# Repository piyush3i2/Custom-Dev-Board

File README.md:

# Custom-Dev-Board
This project focuses on designing and building a custom development board that combines the strengths of the Raspberry Pi RP2040 microcontroller and an Espressif Systems ESP32 Wi-Fi/Bluetooth module on a single PCB. The goal is to create a compact, flexible, and cost-effective devboard suitable for IoT, embedded systems.

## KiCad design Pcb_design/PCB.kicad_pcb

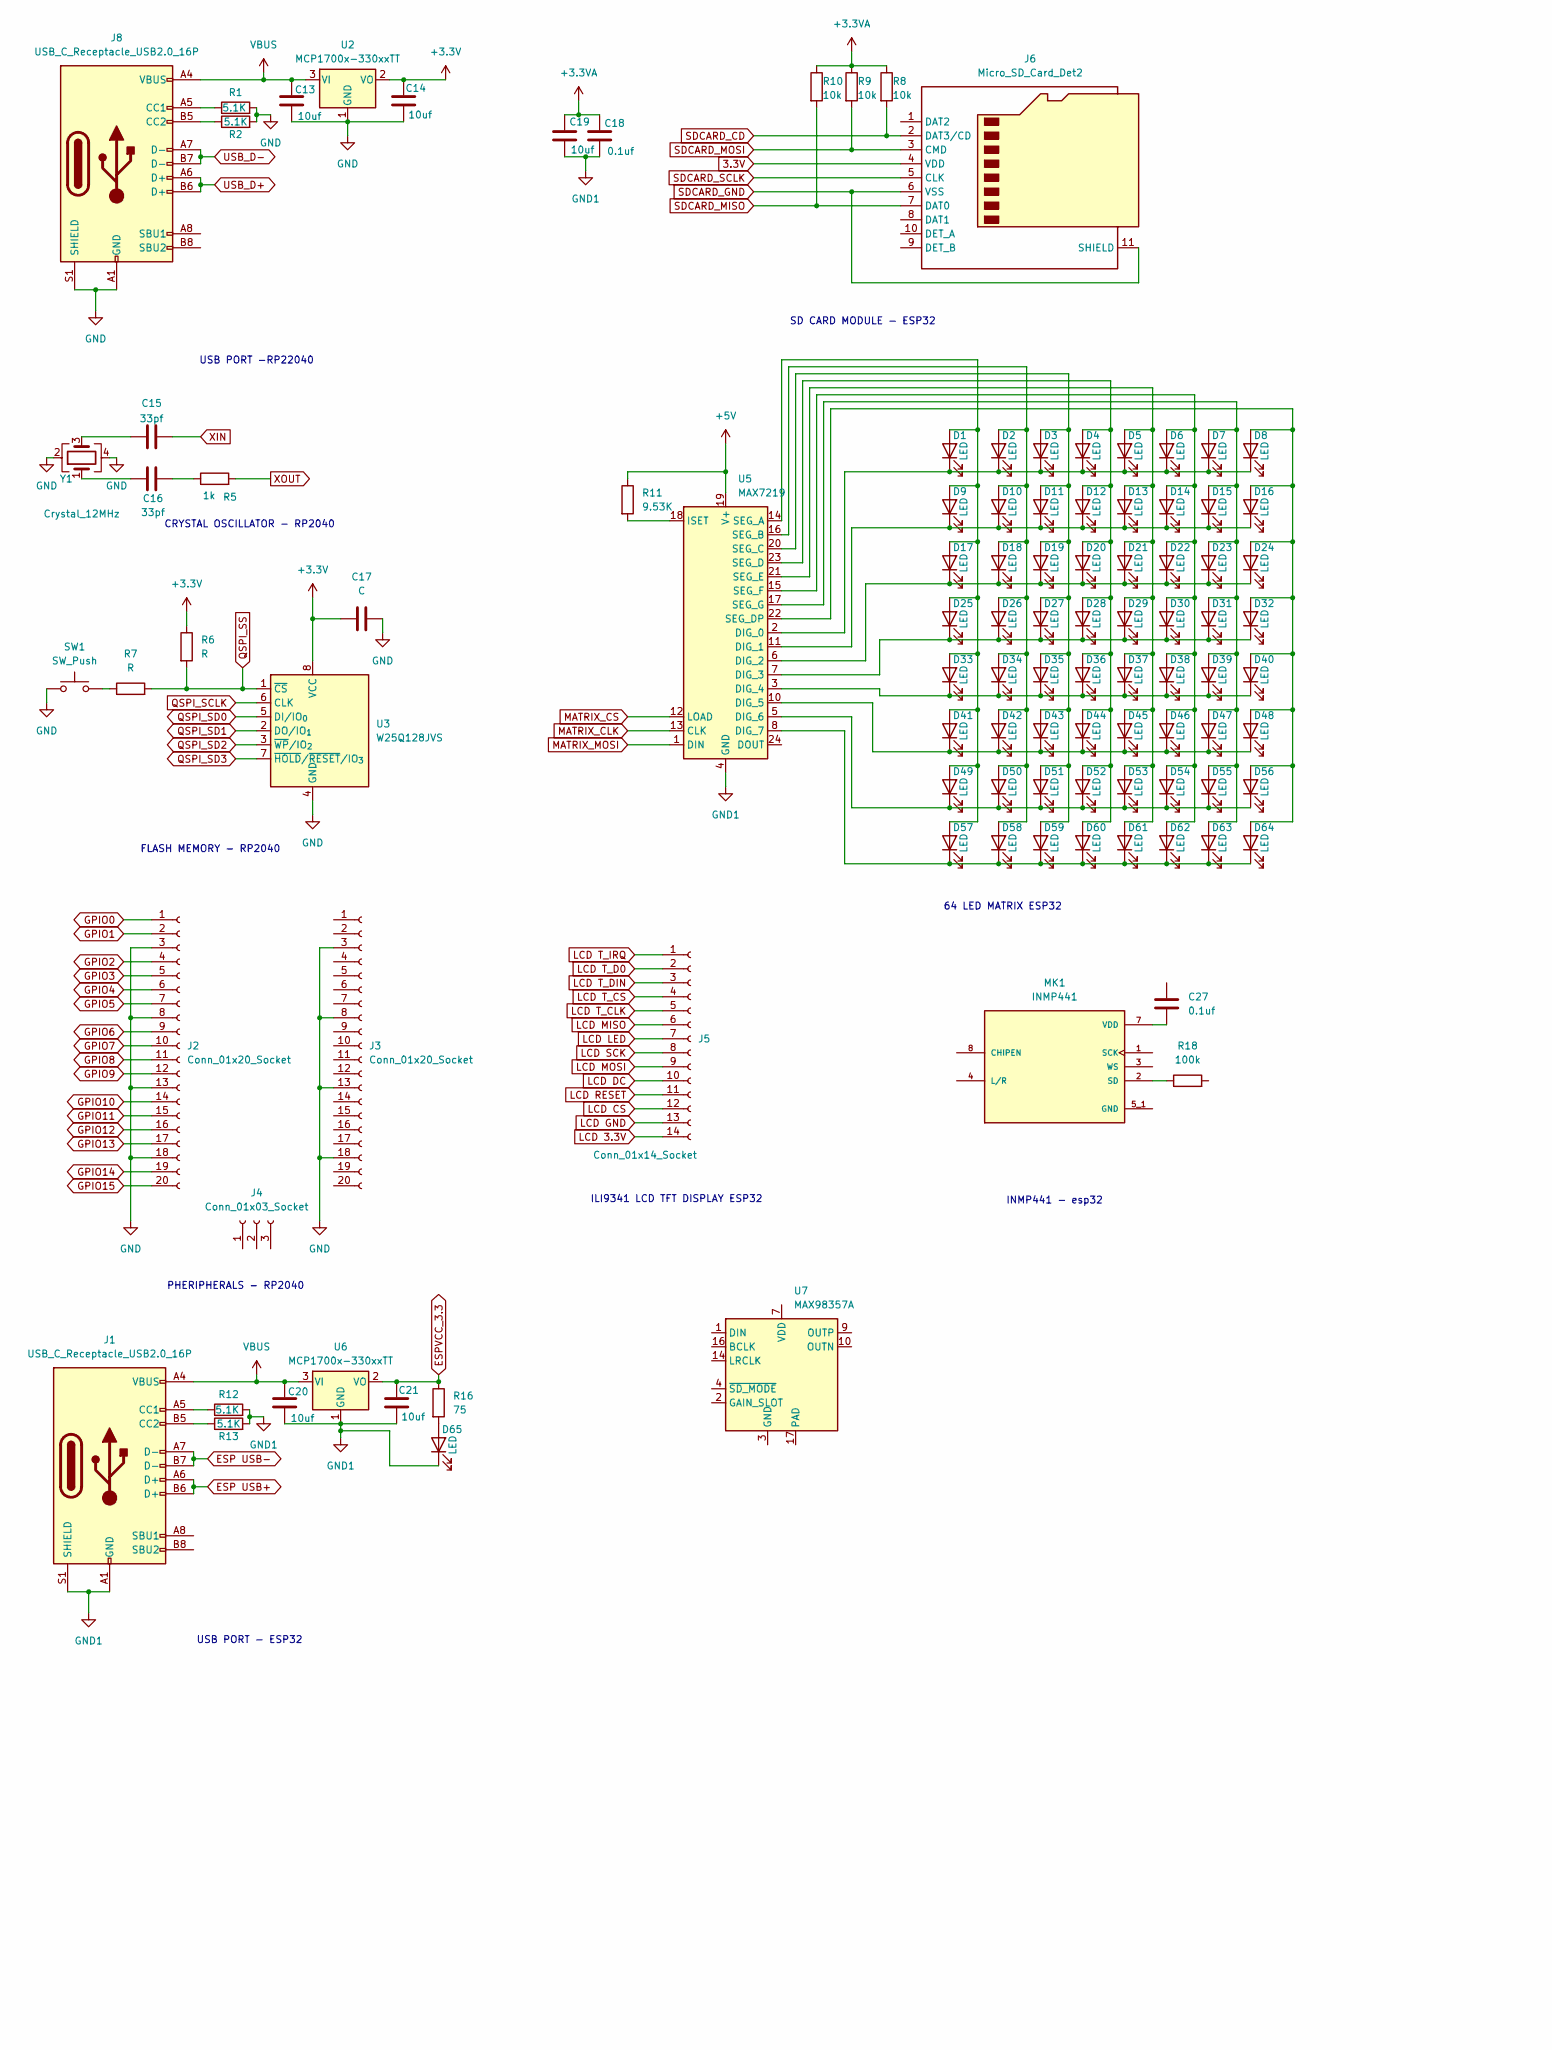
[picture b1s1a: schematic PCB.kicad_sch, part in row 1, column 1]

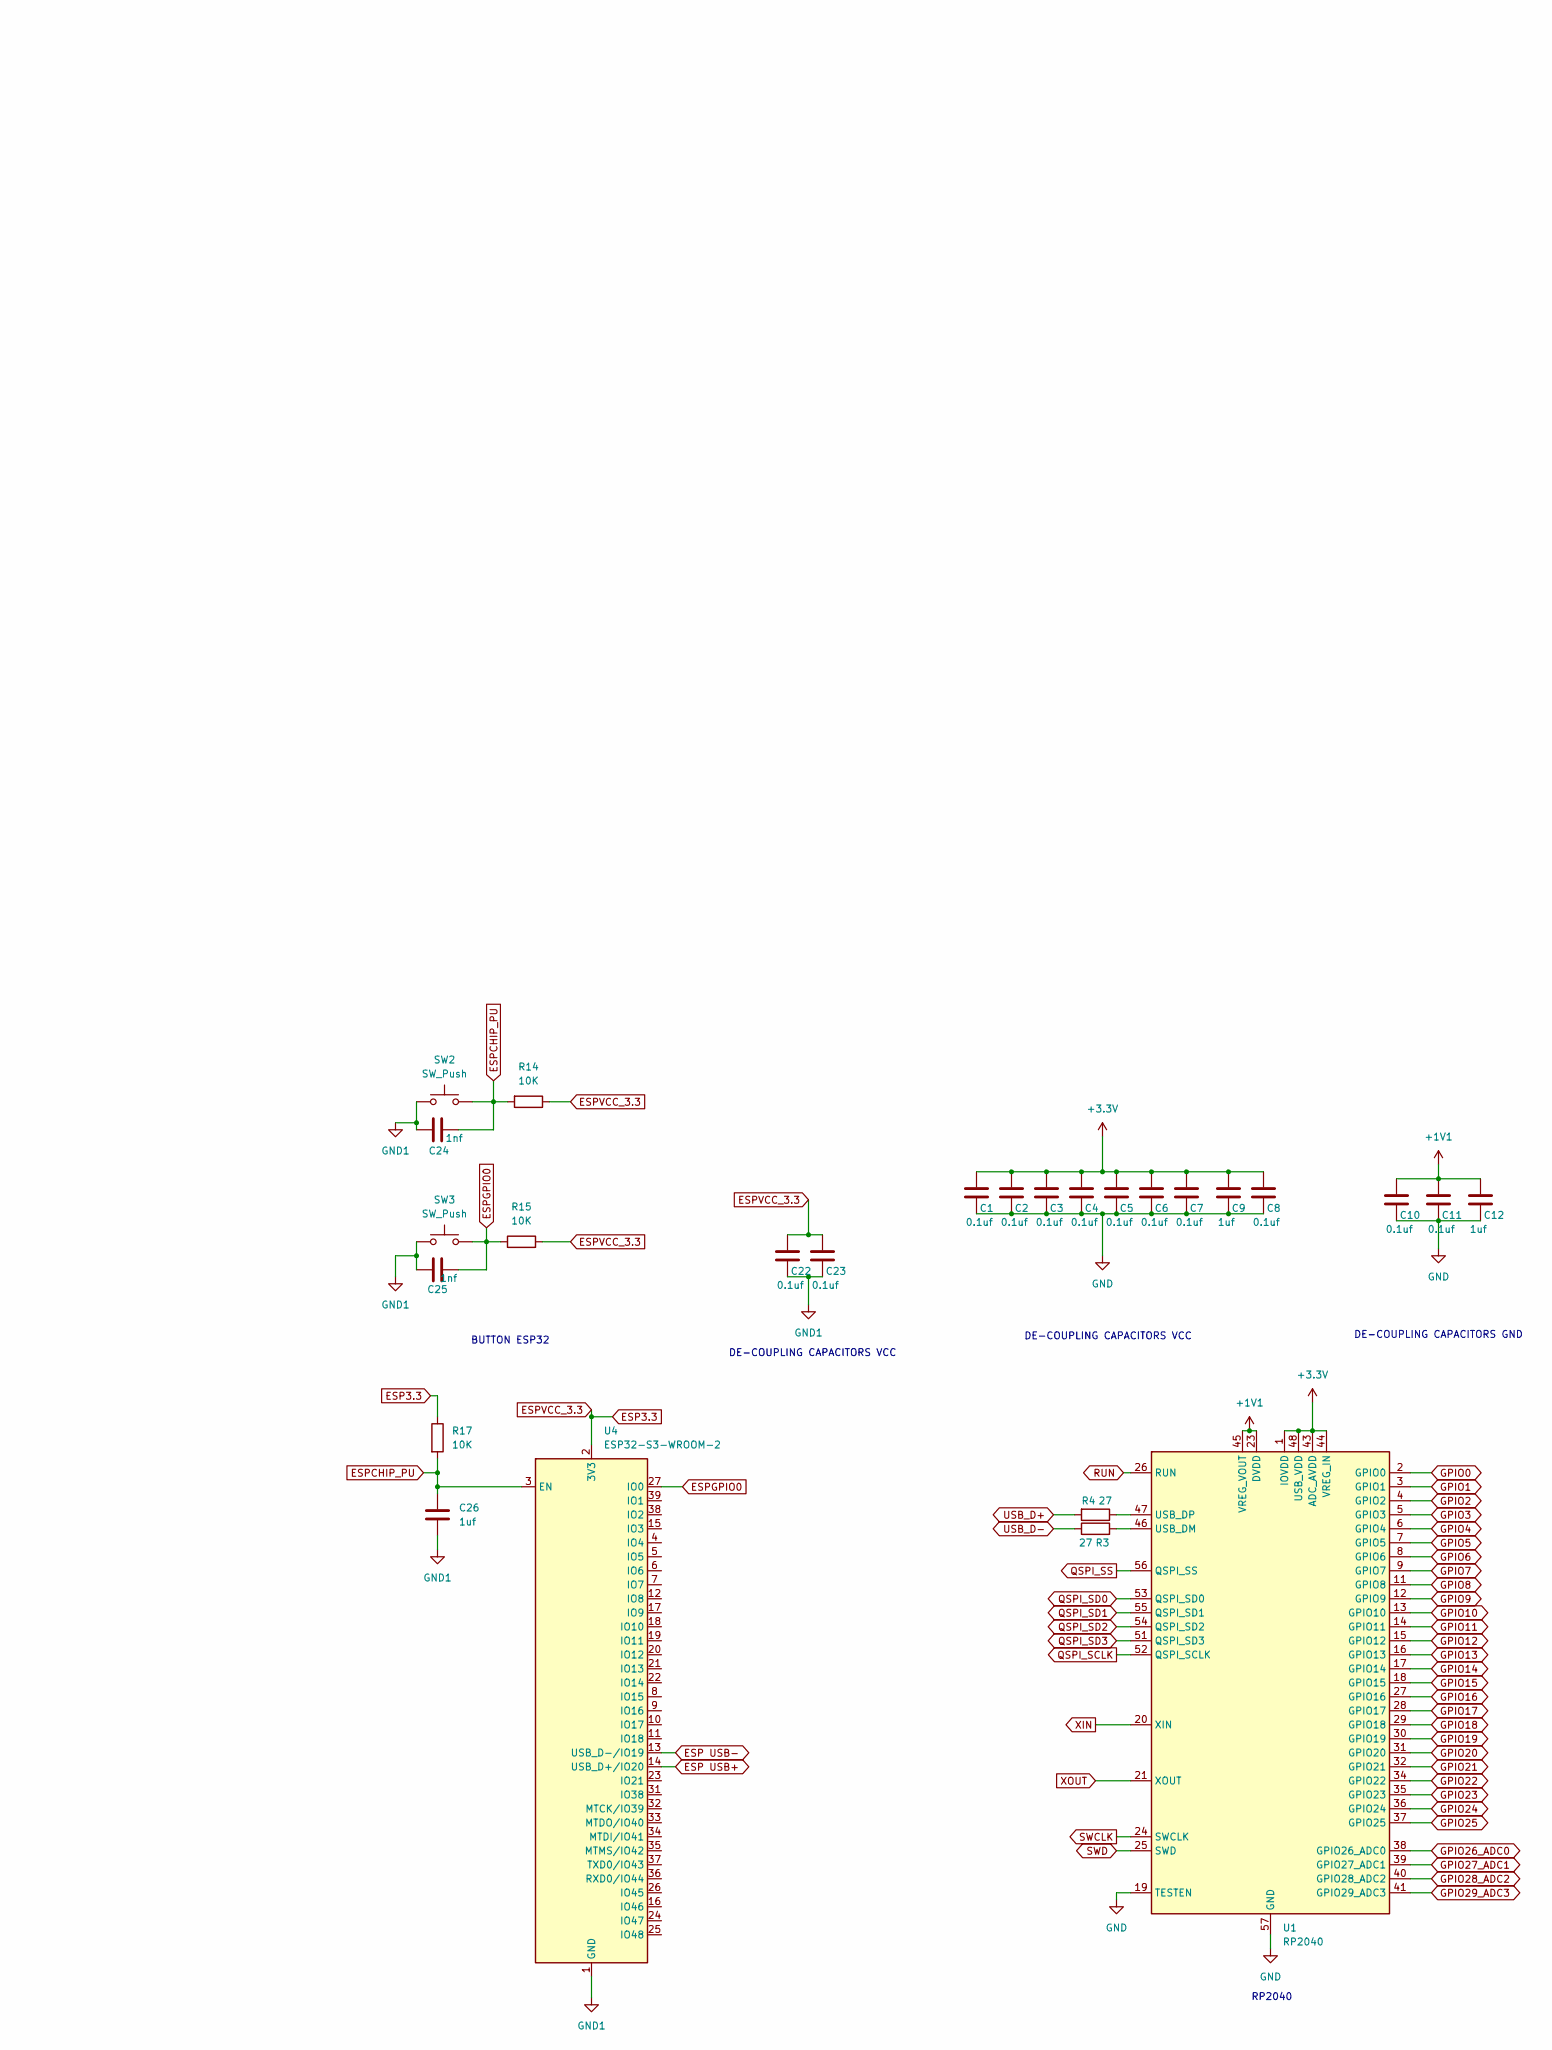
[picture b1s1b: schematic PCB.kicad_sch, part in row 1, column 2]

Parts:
C1, C2, C3, C4, C5, C6, C7, C8, C10, C11, C18, C22, C23, C27: 0.1uf; C_0201_0603Metric_Pad0.64x0.40mm_HandSolder
C9, C12, C26: 1uf; C_0201_0603Metric_Pad0.64x0.40mm_HandSolder
C13, C14, C19, C20, C21: 10uf; C_0201_0603Metric_Pad0.64x0.40mm_HandSolder
C15, C16: 33pf; C_0201_0603Metric_Pad0.64x0.40mm_HandSolder
C17: C; C_0201_0603Metric_Pad0.64x0.40mm_HandSolder
C24, C25: 1nf; C_0201_0603Metric_Pad0.64x0.40mm_HandSolder
D1, D2, D3, D4, D5, D6, D7, D8, D9, D10, D11, D12, D13, D14, D15, D16, D17, D18, D19, D20, D21, D22, D23, D24, D25, D26, D27, D28, D29, D30, D31, D32, D33, D34, D35, D36, D37, D38, D39, D40, D41, D42, D43, D44, D45, D46, D47, D48, D49, D50, D51, D52, D53, D54, D55, D56, D57, D58, D59, D60, D61, D62, D63, D64, D65: LED; LED_0402_1005Metric_Pad0.77x0.64mm_HandSolder
J1, J8: USB_C_Receptacle_USB2.0_16P
J2, J3: Conn_01x20_Socket; PinSocket_1x20_P2.54mm_Vertical
J4: Conn_01x03_Socket; PinSocket_1x03_P2.54mm_Vertical
J5: Conn_01x14_Socket; PinSocket_1x14_P2.54mm_Vertical
J6: Micro_SD_Card_Det2
MK1: INMP441; MIC_INMP441; PARTREV 1.1
R1, R2, R12, R13: 5.1K; R_0201_0603Metric_Pad0.64x0.40mm_HandSolder
R3, R4: 27; R_0201_0603Metric_Pad0.64x0.40mm_HandSolder
R5: 1k; R_0201_0603Metric_Pad0.64x0.40mm_HandSolder
R6, R7: R; R_0201_0603Metric_Pad0.64x0.40mm_HandSolder
R8, R9, R10: 10k; R_0201_0603Metric_Pad0.64x0.40mm_HandSolder
R11: 9.53K; R_0201_0603Metric_Pad0.64x0.40mm_HandSolder
R14, R15, R17: 10K; R_0201_0603Metric_Pad0.64x0.40mm_HandSolder
R16: 75; R_0201_0603Metric_Pad0.64x0.40mm_HandSolder
R18: 100k; R_0201_0603Metric_Pad0.64x0.40mm_HandSolder
SW1, SW2, SW3: SW_Push; R_0201_0603Metric_Pad0.64x0.40mm_HandSolder
U1: RP2040; QFN-56-1EP_7x7mm_P0.4mm_EP3.2x3.2mm
U2, U6: MCP1700x-330xxTT; SOT-23
U3: W25Q128JVS; SOIC-8_5.3x5.3mm_P1.27mm
U4: ESP32-S3-WROOM-2
U5: MAX7219
U7: MAX98357A; TQFN-16-1EP_3x3mm_P0.5mm_EP1.23x1.23mm
Y1: Crystal_12MHz; Crystal_DS10_D1.0mm_L4.3mm_Horizontal_1EP_style1

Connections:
+1V1: C10.1, C11.1, C12.1, U1.23 (DVDD), U1.45 (VREG_VOUT), U1.50 (DVDD)
+3.3V: C1.1, C2.1, C3.1, C4.1, C5.1, C6.1, C7.1, C8.1, C9.1, C14.1, C17.1, R6.1, U1.1 (IOVDD), U1.10 (IOVDD), U1.22 (IOVDD), U1.33 (IOVDD), U1.42 (IOVDD), U1.43 (ADC_AVDD), U1.44 (VREG_IN), U1.48 (USB_VDD), U1.49 (IOVDD), U2.2 (VO), U3.8 (VCC)
+3.3VA: C18.1, C19.1, R8.1, R9.1, R10.1
+5V: R11.1, U5.19 (V+)
ESP3.3: C21.1, C22.1, C23.1, R14.1, R15.2, R16.1, R17.1, U4.2 (3V3), U6.2 (VO)
ESP USB+: J1.A6 (D+), J1.B6 (D+), U4.14 (USB_D+/IO20)
ESP USB-: J1.A7 (D-), J1.B7 (D-), U4.13 (USB_D-/IO19)
ESPCHIP_PU: C24.2, C26.1, R14.2, R17.2, SW2.2, U4.3 (EN)
ESPGPIO0: C25.2, R15.1, SW3.2, U4.27 (IO0)
GND1: C18.2, C19.2, C20.2, C21.2, C22.2, C23.2, C24.1, C25.1, C26.2, D65.1 (K), J1.A1 (GND), J1.A12 (GND), J1.B1 (GND), J1.B12 (GND), J1.S1 (SHIELD), R12.2, R13.2, SW2.1, SW3.1, U4.1 (GND), U4.40 (GND), U4.41 (GND), U5.4 (GND), U5.9 (GND), U6.1 (GND)
GPIO0: J2.1, U1.2 (GPIO0)
GPIO1: J2.2, U1.3 (GPIO1)
GPIO2: J2.4, U1.4 (GPIO2)
GPIO3: J2.5, U1.5 (GPIO3)
GPIO4: J2.6, U1.6 (GPIO4)
GPIO5: J2.7, U1.7 (GPIO5)
GPIO6: J2.9, U1.8 (GPIO6)
GPIO7: J2.10, U1.9 (GPIO7)
GPIO8: J2.11, U1.11 (GPIO8)
GPIO9: J2.12, U1.12 (GPIO9)
GPIO10: J2.14, U1.13 (GPIO10)
GPIO11: J2.15, U1.14 (GPIO11)
GPIO12: J2.16, U1.15 (GPIO12)
GPIO13: J2.17, U1.16 (GPIO13)
GPIO14: J2.19, U1.17 (GPIO14)
GPIO15: J2.20, U1.18 (GPIO15)
GPIO16: U1.27 (GPIO16)
GPIO17: U1.28 (GPIO17)
GPIO18: U1.29 (GPIO18)
GPIO19: U1.30 (GPIO19)
GPIO20: U1.31 (GPIO20)
GPIO21: U1.32 (GPIO21)
GPIO22: U1.34 (GPIO22)
GPIO23: U1.35 (GPIO23)
GPIO24: U1.36 (GPIO24)
GPIO25: U1.37 (GPIO25)
GPIO26_ADC0: U1.38 (GPIO26_ADC0)
GPIO27_ADC1: U1.39 (GPIO27_ADC1)
GPIO28_ADC2: U1.40 (GPIO28_ADC2)
GPIO29_ADC3: U1.41 (GPIO29_ADC3)
LCD 3.3V: J5.14
LCD CS: J5.12
LCD DC: J5.10
LCD GND: J5.13
LCD LED: J5.7
LCD MISO: J5.6
LCD MOSI: J5.9
LCD RESET: J5.11
LCD SCK: J5.8
LCD T_CLK: J5.5
LCD T_CS: J5.4
LCD T_D0: J5.2
LCD T_DIN: J5.3
LCD T_IRQ: J5.1
unnamed: C15.1, Y1.3
unnamed: C16.1, R5.1
unnamed: C16.2, Y1.1
unnamed: D1.2 (A), D9.2 (A), D17.2 (A), D25.2 (A), D33.2 (A), D41.2 (A), D49.2 (A), D57.2 (A), U5.14 (SEG_A)
unnamed: D1.1 (K), D2.1 (K), D3.1 (K), D4.1 (K), D5.1 (K), D6.1 (K), D7.1 (K), D8.1 (K), U5.2 (DIG_0)
unnamed: D2.2 (A), D10.2 (A), D18.2 (A), D26.2 (A), D34.2 (A), D42.2 (A), D50.2 (A), D58.2 (A), U5.16 (SEG_B)
unnamed: D9.1 (K), D10.1 (K), D11.1 (K), D12.1 (K), D13.1 (K), D14.1 (K), D15.1 (K), D16.1 (K), U5.11 (DIG_1)
unnamed: D3.2 (A), D11.2 (A), D19.2 (A), D27.2 (A), D35.2 (A), D43.2 (A), D51.2 (A), D59.2 (A), U5.20 (SEG_C)
unnamed: D4.2 (A), D12.2 (A), D20.2 (A), D28.2 (A), D36.2 (A), D44.2 (A), D52.2 (A), D60.2 (A), U5.23 (SEG_D)
unnamed: D5.2 (A), D13.2 (A), D21.2 (A), D29.2 (A), D37.2 (A), D45.2 (A), D53.2 (A), D61.2 (A), U5.21 (SEG_E)
unnamed: D6.2 (A), D14.2 (A), D22.2 (A), D30.2 (A), D38.2 (A), D46.2 (A), D54.2 (A), D62.2 (A), U5.15 (SEG_F)
unnamed: D7.2 (A), D15.2 (A), D23.2 (A), D31.2 (A), D39.2 (A), D47.2 (A), D55.2 (A), D63.2 (A), U5.17 (SEG_G)
unnamed: D8.2 (A), D16.2 (A), D24.2 (A), D32.2 (A), D40.2 (A), D48.2 (A), D56.2 (A), D64.2 (A), U5.22 (SEG_DP)
unnamed: D17.1 (K), D18.1 (K), D19.1 (K), D20.1 (K), D21.1 (K), D22.1 (K), D23.1 (K), D24.1 (K), U5.6 (DIG_2)
unnamed: D25.1 (K), D26.1 (K), D27.1 (K), D28.1 (K), D29.1 (K), D30.1 (K), D31.1 (K), D32.1 (K), U5.7 (DIG_3)
unnamed: D33.1 (K), D34.1 (K), D35.1 (K), D36.1 (K), D37.1 (K), D38.1 (K), D39.1 (K), D40.1 (K), U5.3 (DIG_4)
unnamed: D41.1 (K), D42.1 (K), D43.1 (K), D44.1 (K), D45.1 (K), D46.1 (K), D47.1 (K), D48.1 (K), U5.10 (DIG_5)
unnamed: D49.1 (K), D50.1 (K), D51.1 (K), D52.1 (K), D53.1 (K), D54.1 (K), D55.1 (K), D56.1 (K), U5.5 (DIG_6)
unnamed: D57.1 (K), D58.1 (K), D59.1 (K), D60.1 (K), D61.1 (K), D62.1 (K), D63.1 (K), D64.1 (K), U5.8 (DIG_7)
unnamed: D65.2 (A), R16.2
unnamed: J1.A5 (CC1), R12.1
unnamed: J1.B5 (CC2), R13.1
unnamed: J6.6 (VSS), J6.11 (SHIELD)
unnamed: J8.A5 (CC1), R1.1
unnamed: J8.B5 (CC2), R2.1
unnamed: MK1.2 (SD), R18.1
unnamed: C27.2, MK1.7 (VDD)
unnamed: R7.1, SW1.2
unnamed: R3.2, U1.46 (USB_DM)
unnamed: R4.1, U1.47 (USB_DP)
unnamed: R11.2, U5.18 (ISET)
unnamed: U7.3 (GND), U7.11 (GND), U7.15 (GND)
unnamed: U7.7 (VDD), U7.8 (VDD)
QSPI_SCLK: U1.52 (QSPI_SCLK), U3.6 (CLK)
QSPI_SD0: U1.53 (QSPI_SD0), U3.5 (DI/IO_{0})
QSPI_SD1: U1.55 (QSPI_SD1), U3.2 (DO/IO_{1})
QSPI_SD2: U1.54 (QSPI_SD2), U3.3 (~WP/IO_{2})
QSPI_SD3: U1.51 (QSPI_SD3), U3.7 (~HOLD/~RESET/IO_{3})
QSPI_SS: R6.2, R7.2, U1.56 (QSPI_SS), U3.1 (~CS)
RUN: U1.26 (RUN)
SDCARD_CD: J6.2 (DAT3/CD), R8.2
SDCARD_MISO: J6.7 (DAT0), R10.2
SDCARD_MOSI: J6.3 (CMD), R9.2
SWCLK: U1.24 (SWCLK)
SWD: U1.25 (SWD)
USB_D+: J8.A6 (D+), J8.B6 (D+), R4.2
USB_D-: J8.A7 (D-), J8.B7 (D-), R3.1
VBUS: C13.1, C20.1, J1.A4 (VBUS), J1.A9 (VBUS), J1.B4 (VBUS), J1.B9 (VBUS), J8.A4 (VBUS), J8.A9 (VBUS), J8.B4 (VBUS), J8.B9 (VBUS), U2.3 (VI), U6.3 (VI)
XIN: C15.2, U1.20 (XIN)
XOUT: R5.2, U1.21 (XOUT)

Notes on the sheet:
64 LED MATRIX ESP32
DE-COUPLING CAPACITORS VCC
USB PORT - ESP32
RP2040
CRYSTAL OSCILLATOR - RP2040
PHERIPHERALS - RP2040
BUTTON ESP32
ILI9341 LCD TFT DISPLAY ESP32
FLASH MEMORY - RP2040
DE-COUPLING CAPACITORS GND
USB PORT -RP22040
SD CARD MODULE - ESP32
INMP441 - esp32

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
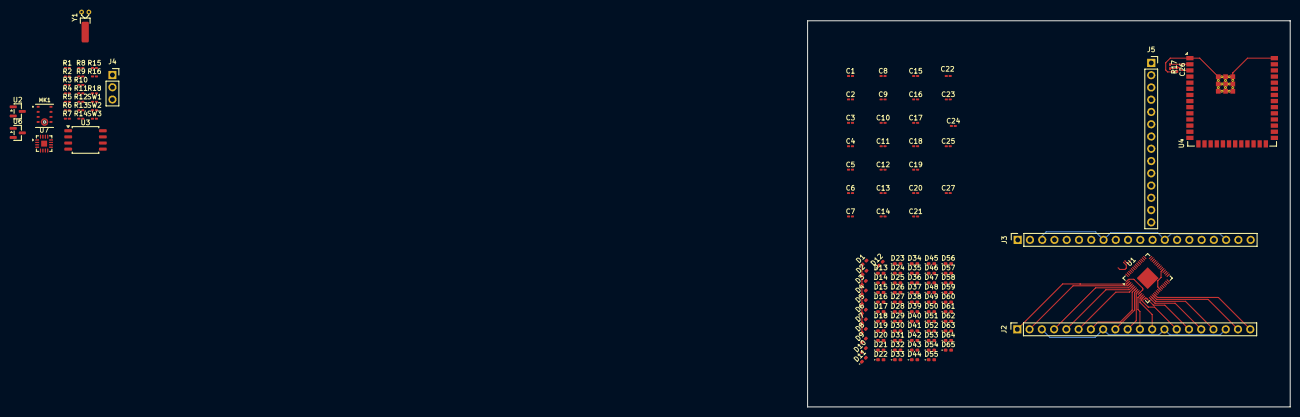
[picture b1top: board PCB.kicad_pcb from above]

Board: 2 copper layers, 100.0 x 80.0 mm, 125 parts (0 on the bottom side), 60 nets.

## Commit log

2026-01-01 Create hi
2026-01-10 Schematic completed
